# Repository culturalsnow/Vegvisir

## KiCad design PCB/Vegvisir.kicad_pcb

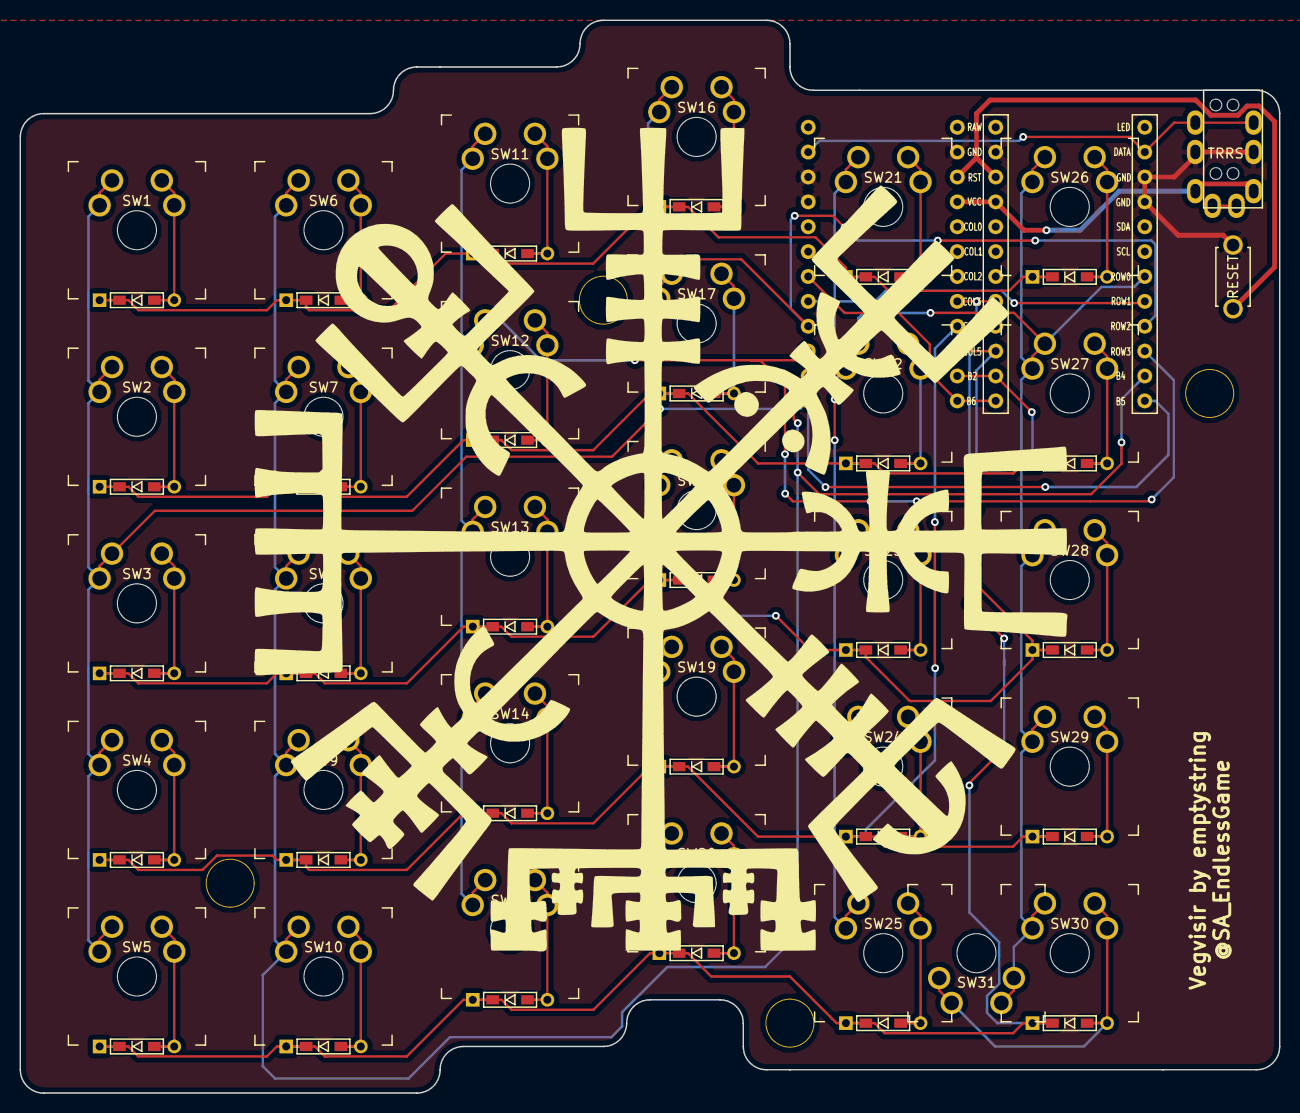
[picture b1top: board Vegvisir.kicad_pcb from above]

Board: 2 copper layers, 128.6 x 109.5 mm, 69 parts (1 on the bottom side), 45 nets.

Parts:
D1, D2, D3, D4, D5, D6, D7, D8, D9, D10, D11, D12, D13, D14, D15, D16, D17, D18, D19, D20, D21, D22, D23, D24, D25, D26, D27, D28, D29, D30: 1N4148; D3_TH_SMD
J1: MJ-4PP-9
Ref**: Val**; HOLE
Ref**#2, Ref**#3, Ref**#4: Val**; HOLE
SW1, SW2, SW3, SW4, SW5, SW6, SW7, SW8, SW9, SW10, SW11, SW12, SW13, SW14, SW15, SW16, SW17, SW18, SW19, SW20, SW21, SW22, SW23, SW24, SW25, SW26, SW27, SW28, SW29, SW30, SW31: SW_PUSH; MX_reversible_minimal
SW32: SW_PUSH; ResetSW
U1, U2: ProMicro; ProMicro_v2_Backside

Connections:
GND: J1.C, SW32.1, U1.3, U1.4, U1.23, U2.3, U2.4, U2.23
unnamed: D1.2, SW1.2
unnamed: D2.2, SW2.2
unnamed: D3.2, SW3.2
unnamed: D4.2, SW4.2
unnamed: D5.2, SW5.2
unnamed: D6.2, SW6.2
unnamed: D7.2, SW7.2
unnamed: D8.2, SW8.2
unnamed: D9.2, SW9.2
unnamed: D10.2, SW10.2
unnamed: D11.2, SW11.2
unnamed: D12.2, SW12.2
unnamed: D13.2, SW13.2
unnamed: D14.2, SW14.2
unnamed: D15.2, SW15.2
unnamed: D16.2, SW16.2
unnamed: D17.2, SW17.2
unnamed: D18.2, SW18.2
unnamed: D19.2, SW19.2
unnamed: D20.2, SW20.2
unnamed: D21.2, SW21.2
unnamed: D22.2, SW22.2
unnamed: D23.2, SW23.2
unnamed: D24.2, SW24.2
unnamed: D25.2, SW25.2
unnamed: D26.2, SW26.2
unnamed: D27.2, SW27.2
unnamed: D28.2, SW28.2
unnamed: D29.2, SW29.2
unnamed: D30.2, SW30.2, SW31.2
VCC: J1.D, U1.21, U2.21
col0: SW1.1, SW2.1, SW3.1, SW4.1, SW5.1, U1.12, U2.12
col1: SW6.1, SW7.1, SW8.1, SW9.1, SW10.1, U1.11, U2.11
col2: SW11.1, SW12.1, SW13.1, SW14.1, SW15.1, U1.10, U2.10
col3: SW16.1, SW17.1, SW18.1, SW19.1, SW20.1, U1.9, U2.9
col4: SW21.1, SW22.1, SW23.1, SW24.1, SW25.1, U1.8, U2.8
col5: SW26.1, SW27.1, SW28.1, SW29.1, SW30.1, SW31.1, U1.7, U2.7
data: J1.B, U1.2, U2.2
reset: SW32.2, U1.22, U2.22
row0: D1.1, D6.1, D11.1, D16.1, D21.1, D26.1, U1.13, U2.13
row1: D2.1, D7.1, D12.1, D17.1, D22.1, D27.1, U1.14, U2.14
row2: D3.1, D8.1, D13.1, D18.1, D23.1, D28.1, U1.15, U2.15
row3: D4.1, D9.1, D14.1, D19.1, D24.1, D29.1, U1.16, U2.16
row4: D5.1, D10.1, D15.1, D20.1, D25.1, D30.1, U1.17, U2.17

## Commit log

2019-03-27 pcb first draft
